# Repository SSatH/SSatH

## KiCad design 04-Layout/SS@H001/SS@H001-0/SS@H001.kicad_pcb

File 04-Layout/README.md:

# SSatH

In this folder you can find the boards design files of project.
In particular the projects are:
* SS@H001
* SS@H002
* SS@H003
* SS@H004 - Tech garden control node.
* SS@H005 - Tech garden sensor node.

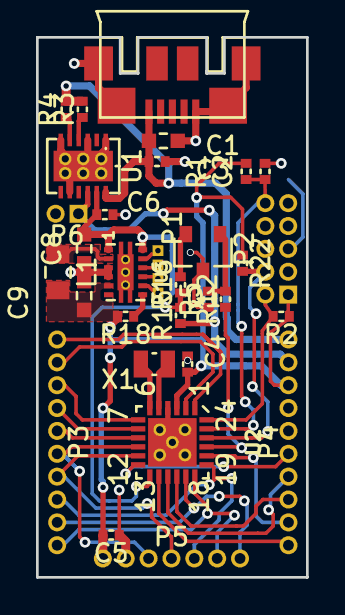
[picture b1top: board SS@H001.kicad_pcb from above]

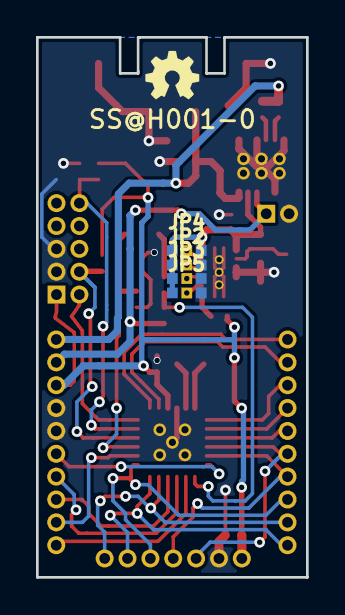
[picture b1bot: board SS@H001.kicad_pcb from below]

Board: 2 copper layers, 15.0 x 30.0 mm, 34 parts (4 on the bottom side), 37 nets.

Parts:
C1, C8, C9: 10uF; 0603
C2, C4, C5: 100nF; 0402
C3: 1uF; 0402
C6: 10uF; 0402
JP2, JP3, JP4, JP5: JUMPER-3; JUMPER-3C
L1: 2.2uH; 0805
P1: MICRO-USB; MICRO-USB-B
P2: SWD; 5x2-1.27mm-Tht
P3, P4: CONN_10; 10x1-1.27mm-Tht
P5: CONN_7; 7x1-1.27mm-Tht
P6: BATT; 2x1-1.27mm-Tht
Q1: MMBF170; SOT23
R1, R2, R22: 10k; 0402
R3: 3.9k; 0402
R4: 4.7k; 0402
R5: 100k; 0402
R12: 0; 0402
R15, R16: 200k; 0402
R18: 1M; 0402
U1: LTC4067; Dfn-12
U2: KL03; Qfn-24
U3: TPS62740; Wson-12
X1: 32.768KHZ; Qtc2

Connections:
+5V: C1.1, C3.1, P1.1, P4.1, R3.2, R4.2, U1.12
+BATT: P4.2, P6.1, R15.1, U1.10
/Ai0: P4.6, U2.12
/Ai1: P4.7, U2.15
/Ai2: P4.8, U2.16
/Ai3: P4.9, U2.20
/Ao0: P4.10, U2.14
/BattDet: R12.1, U2.21
/Dio0: P3.1, U2.1
/Dio1: P3.2, U2.2
/Dio2: P3.3, U2.7
/Dio3: P3.4, U2.8
/Dio4: P3.5, U2.9
/Dio5: P3.6, P5.3, U2.10
/Dio6: P3.7, P5.4, U2.11
/Dio7: P3.8, P5.5, U2.19
/Extal0: U2.5, X1.1
/SwdClk: P2.4, R22.2, U2.22
/SwdDio: P2.2, R2.2, U2.24
/Swd~Reset: C2.1, P2.10, R1.2, U2.23
/UartRx: P3.10, P5.6, U2.18
/UartTx: P3.9, P5.7, U2.17
/Vbat: R15.2, R16.1, U2.13
/Xtal0: U2.6, X1.2
GND: C1.2, C2.2, C3.2, C4.2, C5.1, C6.2, C8.1, C9.2, JP2.3, JP3.3, JP4.3, JP5.3, P1.5, P2.3, P2.5, P4.4, P4.5, P5.2, P6.2, Q1.3, R5.1, U1.1, U1.3, U1.6, U1.8, U1.Ep, U2.4, U2.Ep, U3.3, U3.4
unnamed: R18.1, U3.7
unnamed: L1.1, U3.2
unnamed: Q1.2, R16.2
unnamed: R3.1, U1.4
unnamed: Q1.1, R5.2, R12.2
unnamed: R4.1, U1.5
unnamed: JP5.2, U3.8
unnamed: JP3.2, U3.9
unnamed: JP2.2, U3.10
unnamed: JP4.2, U3.11
unnamed: C6.1, C8.2, JP2.1, JP3.1, JP4.1, JP5.1, U1.11, U3.1, U3.12
VCC: C4.1, C5.2, C9.1, L1.2, P2.1, P4.3, P5.1, R1.1, R2.1, R18.2, R22.1, U2.3, U3.5

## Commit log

2015-08-10 Added node board firmware project based on FRDM-KL25Z
2015-08-10 Moved firmware files into right folder and added readme and license files for each folder.
2015-08-10 Moved firmware project.
2015-08-10 Added SS@H001-0.
2015-08-10 Deleted temporary files.
